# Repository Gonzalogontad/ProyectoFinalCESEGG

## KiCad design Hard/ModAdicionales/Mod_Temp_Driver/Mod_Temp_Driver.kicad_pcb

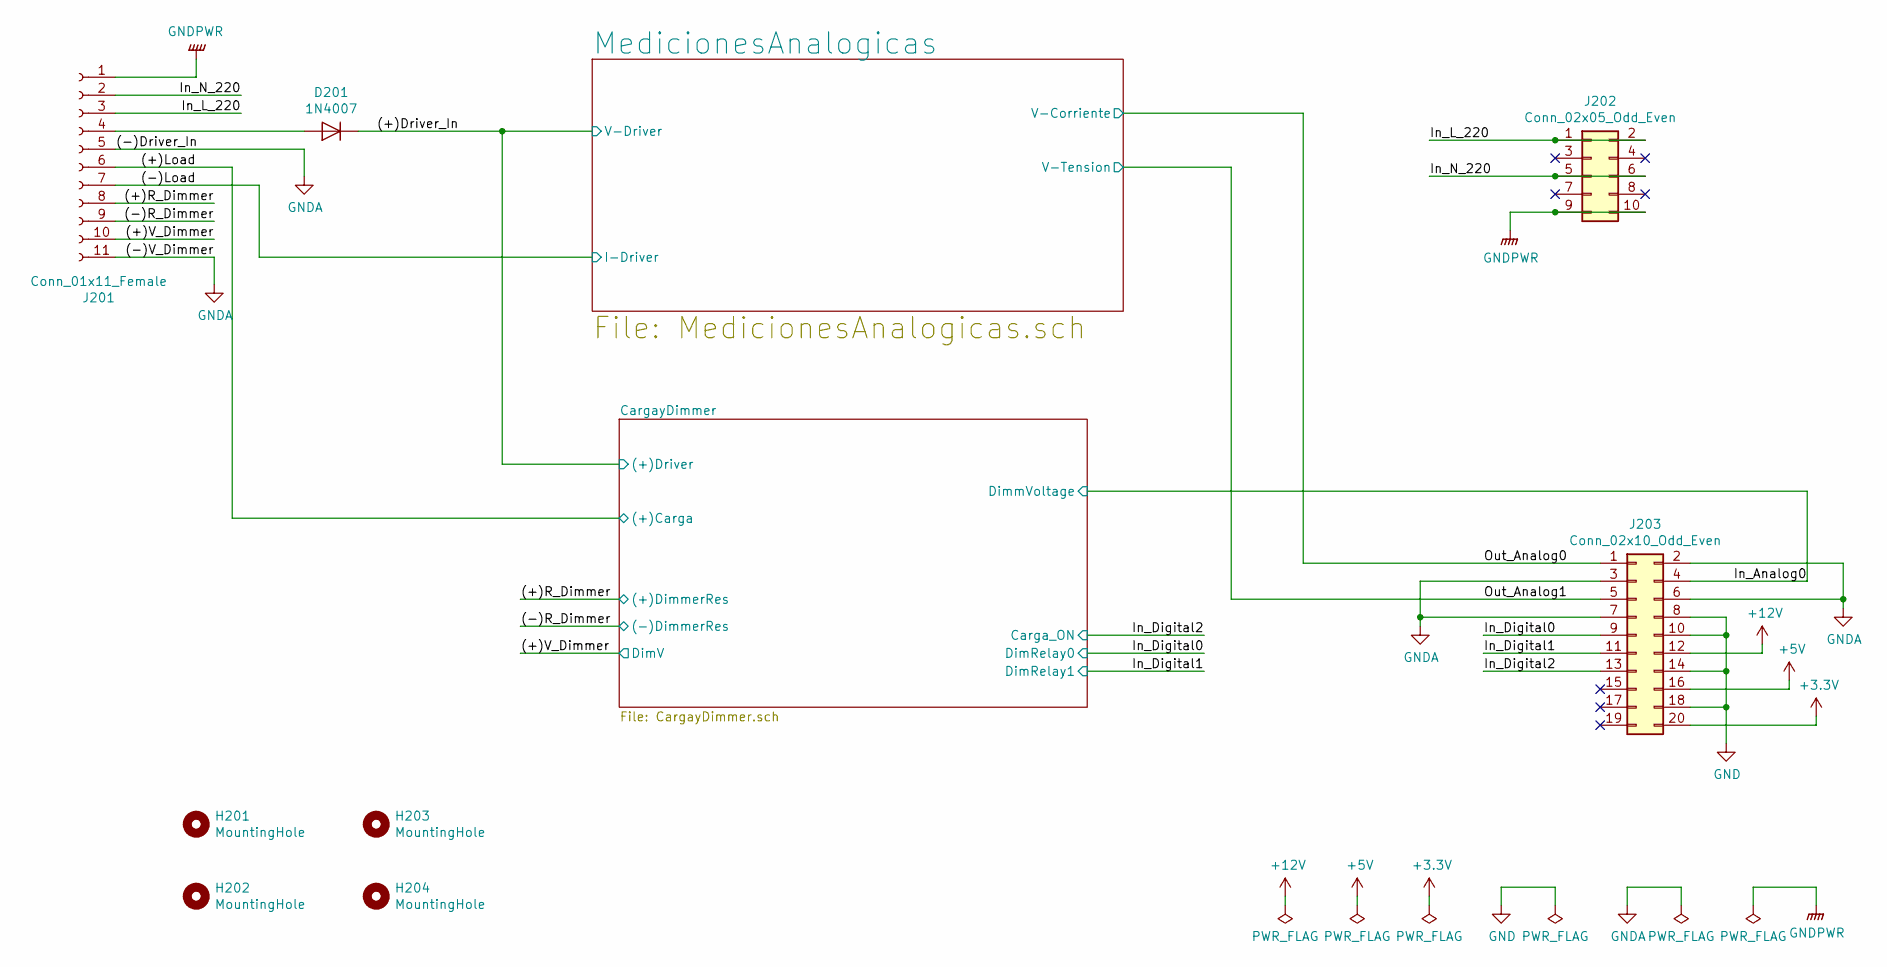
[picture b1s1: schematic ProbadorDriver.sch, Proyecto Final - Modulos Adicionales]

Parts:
D201: 1N4007; D_DO-41_SOD81_P10.16mm_Horizontal
H201, H202, H203, H204: MountingHole; MountingHole_3.2mm_M3
J201: Conn_01x11_Female; TerminalBlock_bornier-11_P5.00mm
J202: Conn_02x05_Odd_Even; PinHeader_2x05_P2.54mm_Horizontal
J203: Conn_02x10_Odd_Even; PinHeader_2x10_P2.54mm_Horizontal

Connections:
+3V3: J203.20
+5V: J203.16
+12V: J203.12; also elsewhere on the board
/ProbadorDriver/(+)Driver_In: D201.1 (K); also elsewhere on the board
/ProbadorDriver/(+)Load: J201.6; also elsewhere on the board
/ProbadorDriver/(+)R_Dimmer: J201.8; also elsewhere on the board
/ProbadorDriver/(+)V_Dimmer: J201.10; also elsewhere on the board
/ProbadorDriver/(-)Load: J201.7; also elsewhere on the board
/ProbadorDriver/(-)R_Dimmer: J201.9; also elsewhere on the board
/ProbadorDriver/In_Analog0: J203.4; also elsewhere on the board
/ProbadorDriver/In_Digital0: J203.9; also elsewhere on the board
/ProbadorDriver/In_Digital1: J203.11; also elsewhere on the board
/ProbadorDriver/In_Digital2: J203.13; also elsewhere on the board
/ProbadorDriver/In_L_220: J201.3, J202.1, J202.2
/ProbadorDriver/In_N_220: J201.2, J202.5, J202.6
/ProbadorDriver/Out_Analog0: J203.1; also elsewhere on the board
/ProbadorDriver/Out_Analog1: J203.5; also elsewhere on the board
GND: J203.8, J203.10, J203.14, J203.18; also elsewhere on the board
GNDA: J201.5, J201.11, J203.2, J203.3, J203.6, J203.7; also elsewhere on the board
GNDPWR: J201.1, J202.9, J202.10
unnamed: D201.2 (A), J201.4

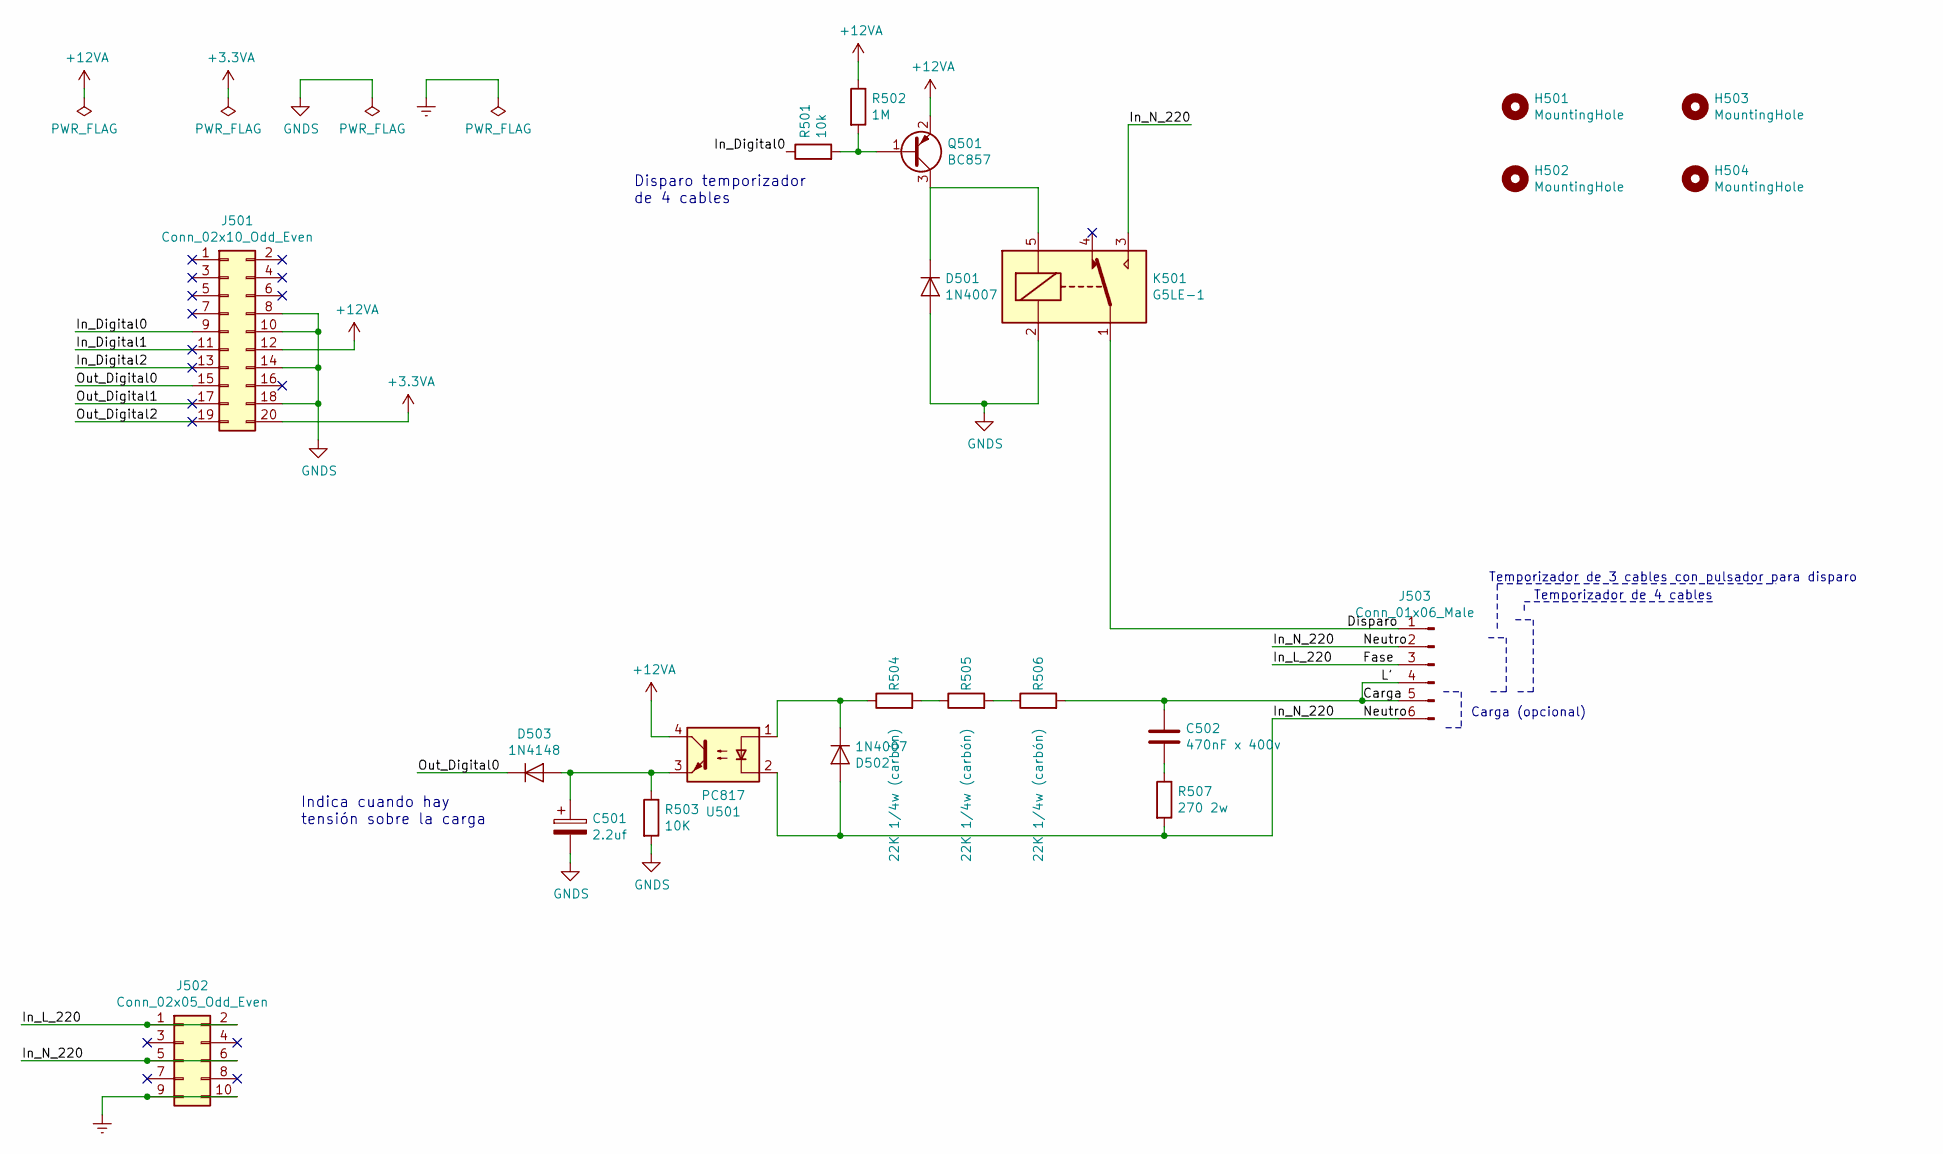
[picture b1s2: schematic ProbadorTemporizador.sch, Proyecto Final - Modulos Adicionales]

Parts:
C501: 2.2uf; CP_Radial_D5.0mm_P2.00mm
C502: 470nF x 400v; C_Rect_L16.5mm_W8.7mm_P15.00mm_MKT
D501, D502: 1N4007; D_DO-41_SOD81_P10.16mm_Horizontal
D503: 1N4148; D_MiniMELF
H501, H502, H503, H504: MountingHole; MountingHole_3.2mm_M3
J501: Conn_02x10_Odd_Even; PinHeader_2x10_P2.54mm_Horizontal
J502: Conn_02x05_Odd_Even; PinHeader_2x05_P2.54mm_Horizontal
J503: Conn_01x06_Male; TerminalBlock_bornier-6_P5.00mm
K501: G5LE-1; Relay_SPDT_Omron-G5LE-1
Q501: BC857; SOT-23
R501: 10k; R_0805_2012Metric_Pad1.15x1.40mm_HandSolder
R502: 1M; R_0805_2012Metric_Pad1.15x1.40mm_HandSolder
R503: 10K; R_0805_2012Metric_Pad1.15x1.40mm_HandSolder
R504, R505, R506: 22K 1/4w (carbón); R_Axial_DIN0207_L6.3mm_D2.5mm_P7.62mm_Horizontal
R507: 270 2w; R_Axial_DIN0516_L15.5mm_D5.0mm_P20.32mm_Horizontal
U501: PC817; DIP-4_W7.62mm

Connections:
+3.3VA: J501.20
+12VA: J501.12, Q501.2 (E), R502.1, U501.4
/ProbadorTemporizador/Carga: C502.1, J503.4, J503.5, R506.2
/ProbadorTemporizador/Disparo: J503.1, K501.1
/ProbadorTemporizador/Fase: J502.1, J502.2, J503.3
/ProbadorTemporizador/In_Digital0: J501.9, R501.1
/ProbadorTemporizador/In_Digital1: J501.11
/ProbadorTemporizador/In_Digital2: J501.13
/ProbadorTemporizador/In_N_220: D502.2 (A), J502.5, J502.6, J503.2, J503.6, K501.3, R507.2, U501.2
/ProbadorTemporizador/Out_Digital0: D503.1 (K), J501.15
/ProbadorTemporizador/Out_Digital1: J501.17
/ProbadorTemporizador/Out_Digital2: J501.19
Earth: J502.9, J502.10
GNDS: C501.2, D501.2 (A), J501.8, J501.10, J501.14, J501.18, K501.2, R503.2
unnamed: C501.1, D503.2 (A), R503.1, U501.3
unnamed: C502.2, R507.1
unnamed: D501.1 (K), K501.5, Q501.3 (C)
unnamed: D502.1 (K), R504.1, U501.1
unnamed: Q501.1 (B), R501.2, R502.2
unnamed: R504.2, R505.1
unnamed: R505.2, R506.1

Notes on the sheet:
Carga (opcional)
Temporizador de 3 cables con pulsador para disparo
Temporizador de 4 cables
Disparo temporizador de 4 cables
Indica cuando hay tensión sobre la carga

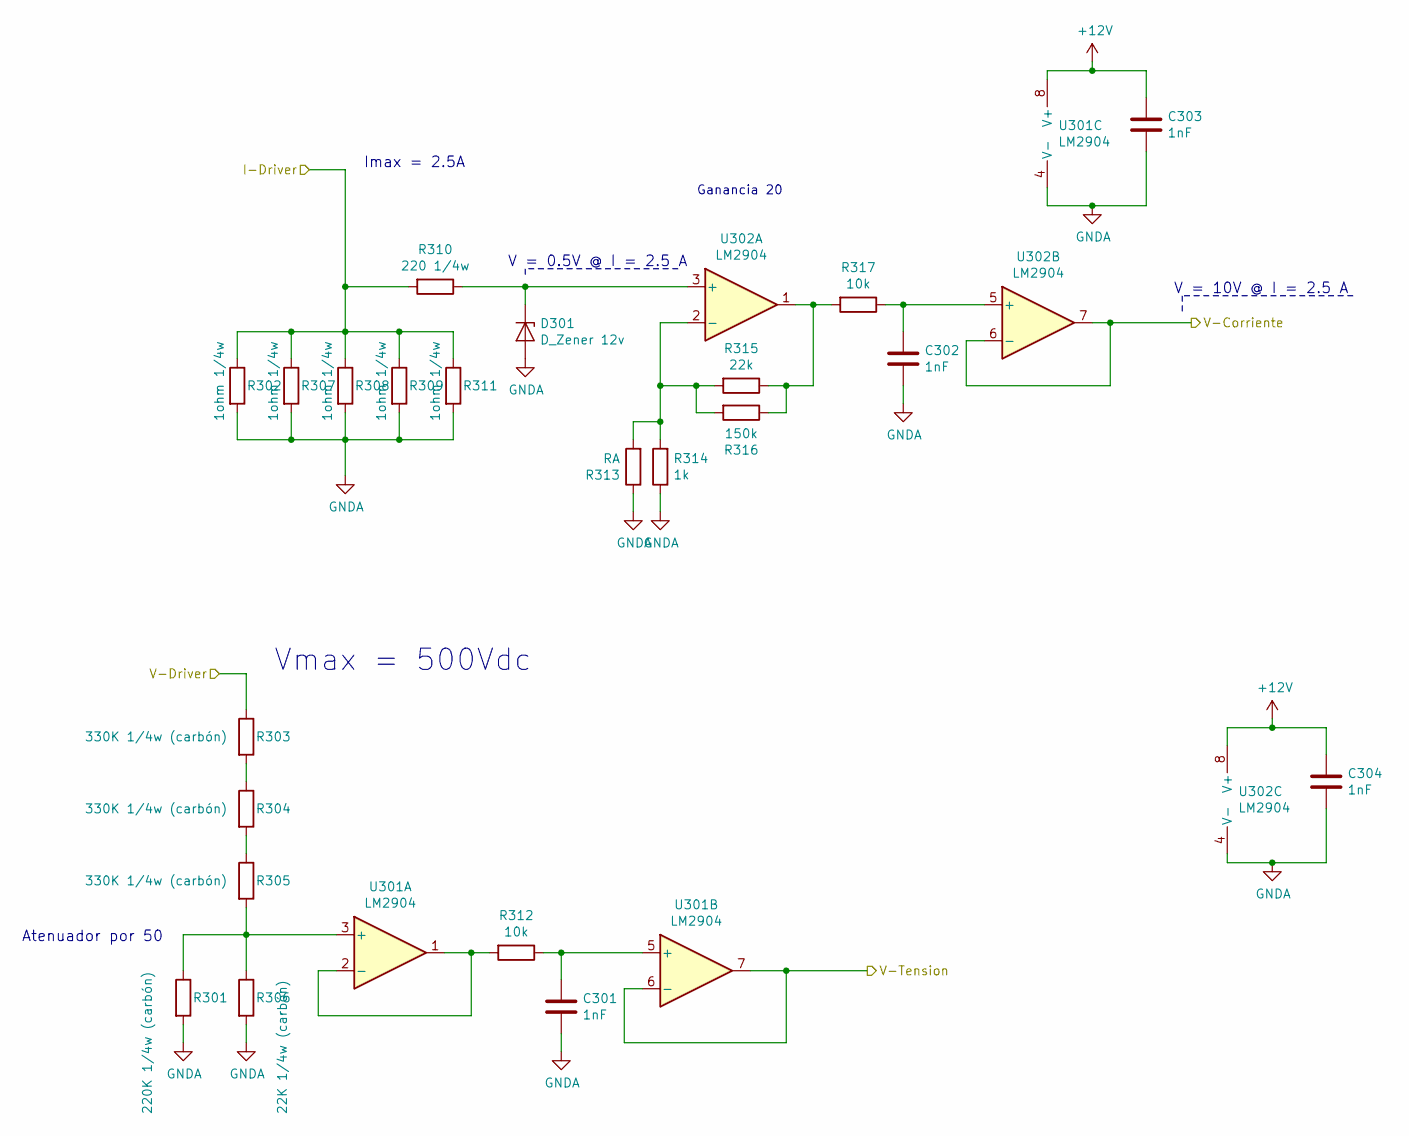
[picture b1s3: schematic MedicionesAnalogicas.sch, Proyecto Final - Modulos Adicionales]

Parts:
C301, C302, C303, C304: 1nF; C_0805_2012Metric_Pad1.15x1.40mm_HandSolder
D301: D_Zener 12v; D_DO-35_SOD27_P7.62mm_Horizontal
R301: 220K 1/4w (carbón); R_Axial_DIN0309_L9.0mm_D3.2mm_P12.70mm_Horizontal
R302, R307, R308, R309, R311: 1ohm 1/4w; R_Axial_DIN0309_L9.0mm_D3.2mm_P12.70mm_Horizontal
R303, R304, R305: 330K 1/4w (carbón); R_Axial_DIN0309_L9.0mm_D3.2mm_P12.70mm_Horizontal
R306: 22K 1/4w (carbón); R_Axial_DIN0309_L9.0mm_D3.2mm_P12.70mm_Horizontal
R310: 220 1/4w; R_Axial_DIN0309_L9.0mm_D3.2mm_P12.70mm_Horizontal
R312, R317: 10k; R_0805_2012Metric_Pad1.15x1.40mm_HandSolder
R313: RA; R_0805_2012Metric_Pad1.15x1.40mm_HandSolder
R314: 1k; R_0805_2012Metric_Pad1.15x1.40mm_HandSolder
R315: 22k; R_0805_2012Metric_Pad1.15x1.40mm_HandSolder
R316: 150k; R_0805_2012Metric_Pad1.15x1.40mm_HandSolder
U301, U302: LM2904; SO-8_3.9x4.9mm_P1.27mm

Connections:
+12V: C303.1, C304.1, U301.8 (V+), U302.8 (V+); also elsewhere on the board
/ProbadorDriver/(+)Driver_In: R303.1; also elsewhere on the board
/ProbadorDriver/(-)Load: R302.1, R307.1, R308.1, R309.1, R310.2, R311.1; also elsewhere on the board
/ProbadorDriver/Out_Analog0: U302.6 (-), U302.7; also elsewhere on the board
/ProbadorDriver/Out_Analog1: U301.6 (-), U301.7; also elsewhere on the board
GNDA: C301.2, C302.2, C303.2, C304.2, D301.2 (A), R301.2, R302.2, R306.2, R307.2, R308.2, R309.2, R311.2, R313.1, R314.1, U301.4 (V-), U302.4 (V-); also elsewhere on the board
unnamed: C301.1, R312.1, U301.5 (+)
unnamed: C302.1, R317.1, U302.5 (+)
unnamed: D301.1 (K), R310.1, U302.3 (+)
unnamed: R301.1, R305.2, R306.1, U301.3 (+)
unnamed: R303.2, R304.1
unnamed: R304.2, R305.1
unnamed: R312.2, U301.1, U301.2 (-)
unnamed: R313.2, R314.2, R315.2, R316.2, U302.2 (-)
unnamed: R315.1, R316.1, R317.2, U302.1

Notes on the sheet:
Ganancia 20
Vmax = 500Vdc
Atenuador por 50
Imax = 2.5A
V = 0.5V @ I = 2.5 A
V = 10V @ I = 2.5 A

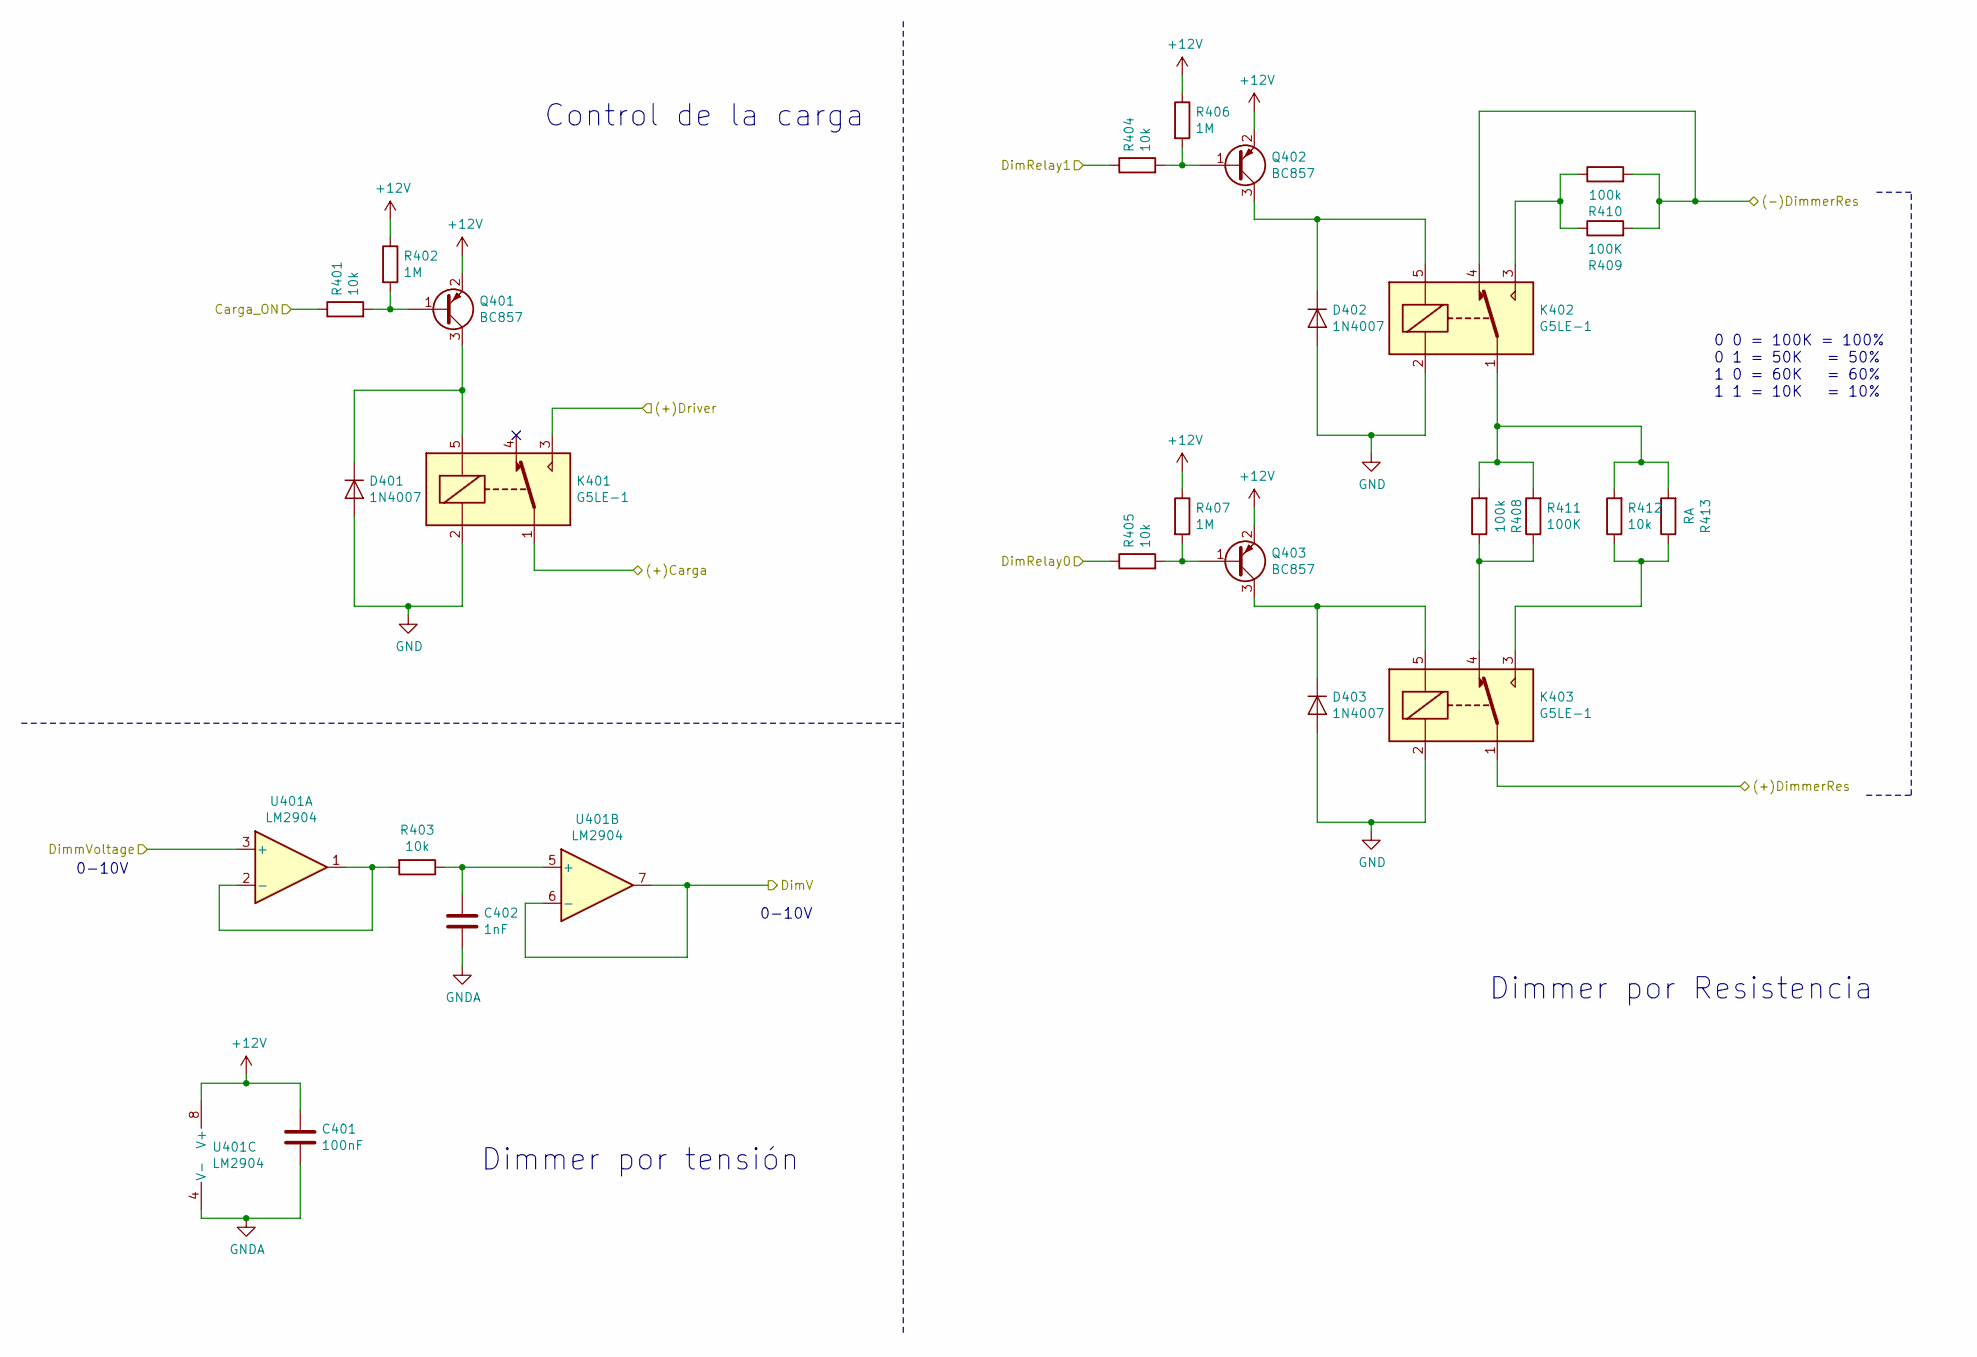
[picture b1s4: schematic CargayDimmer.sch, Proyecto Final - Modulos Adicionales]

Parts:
C401: 100nF; C_0805_2012Metric_Pad1.15x1.40mm_HandSolder
C402: 1nF; C_0805_2012Metric_Pad1.15x1.40mm_HandSolder
D401, D402, D403: 1N4007; D_DO-41_SOD81_P10.16mm_Horizontal
K401, K402, K403: G5LE-1; Relay_SPDT_Omron-G5LE-1
Q401, Q402, Q403: BC857; SOT-23
R401, R403, R404, R405, R412: 10k; R_0805_2012Metric_Pad1.15x1.40mm_HandSolder
R402, R406, R407: 1M; R_0805_2012Metric_Pad1.15x1.40mm_HandSolder
R408, R410: 100k; R_0805_2012Metric_Pad1.15x1.40mm_HandSolder
R409, R411: 100K; R_0805_2012Metric_Pad1.15x1.40mm_HandSolder
R413: RA; R_0805_2012Metric_Pad1.15x1.40mm_HandSolder
U401: LM2904; SO-8_3.9x4.9mm_P1.27mm

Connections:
+12V: C401.1, Q401.2 (E), Q402.2 (E), Q403.2 (E), R402.1, R406.1, R407.1, U401.8 (V+); also elsewhere on the board
/ProbadorDriver/(+)Driver_In: K401.3; also elsewhere on the board
/ProbadorDriver/(+)Load: K401.1; also elsewhere on the board
/ProbadorDriver/(+)R_Dimmer: K403.1; also elsewhere on the board
/ProbadorDriver/(+)V_Dimmer: U401.6 (-), U401.7; also elsewhere on the board
/ProbadorDriver/(-)R_Dimmer: K402.4, R409.2, R410.2; also elsewhere on the board
/ProbadorDriver/In_Analog0: U401.3 (+); also elsewhere on the board
/ProbadorDriver/In_Digital0: R405.1; also elsewhere on the board
/ProbadorDriver/In_Digital1: R404.1; also elsewhere on the board
/ProbadorDriver/In_Digital2: R401.1; also elsewhere on the board
GND: D401.2 (A), D402.2 (A), D403.2 (A), K401.2, K402.2, K403.2; also elsewhere on the board
GNDA: C401.2, C402.2, U401.4 (V-); also elsewhere on the board
unnamed: C402.1, R403.1, U401.5 (+)
unnamed: D401.1 (K), K401.5, Q401.3 (C)
unnamed: D402.1 (K), K402.5, Q402.3 (C)
unnamed: D403.1 (K), K403.5, Q403.3 (C)
unnamed: K402.1, R408.2, R411.2, R412.2, R413.2
unnamed: K402.3, R409.1, R410.1
unnamed: K403.3, R412.1, R413.1
unnamed: K403.4, R408.1, R411.1
unnamed: Q401.1 (B), R401.2, R402.2
unnamed: Q402.1 (B), R404.2, R406.2
unnamed: Q403.1 (B), R405.2, R407.2
unnamed: R403.2, U401.1, U401.2 (-)

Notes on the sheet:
Control de la carga
Dimmer por tensión
Dimmer por Resistencia
0-10V
0 0 = 100K = 100% 0 1 = 50K = 50% 1 0 = 60K = 60% 1 1 = 10K = 10%

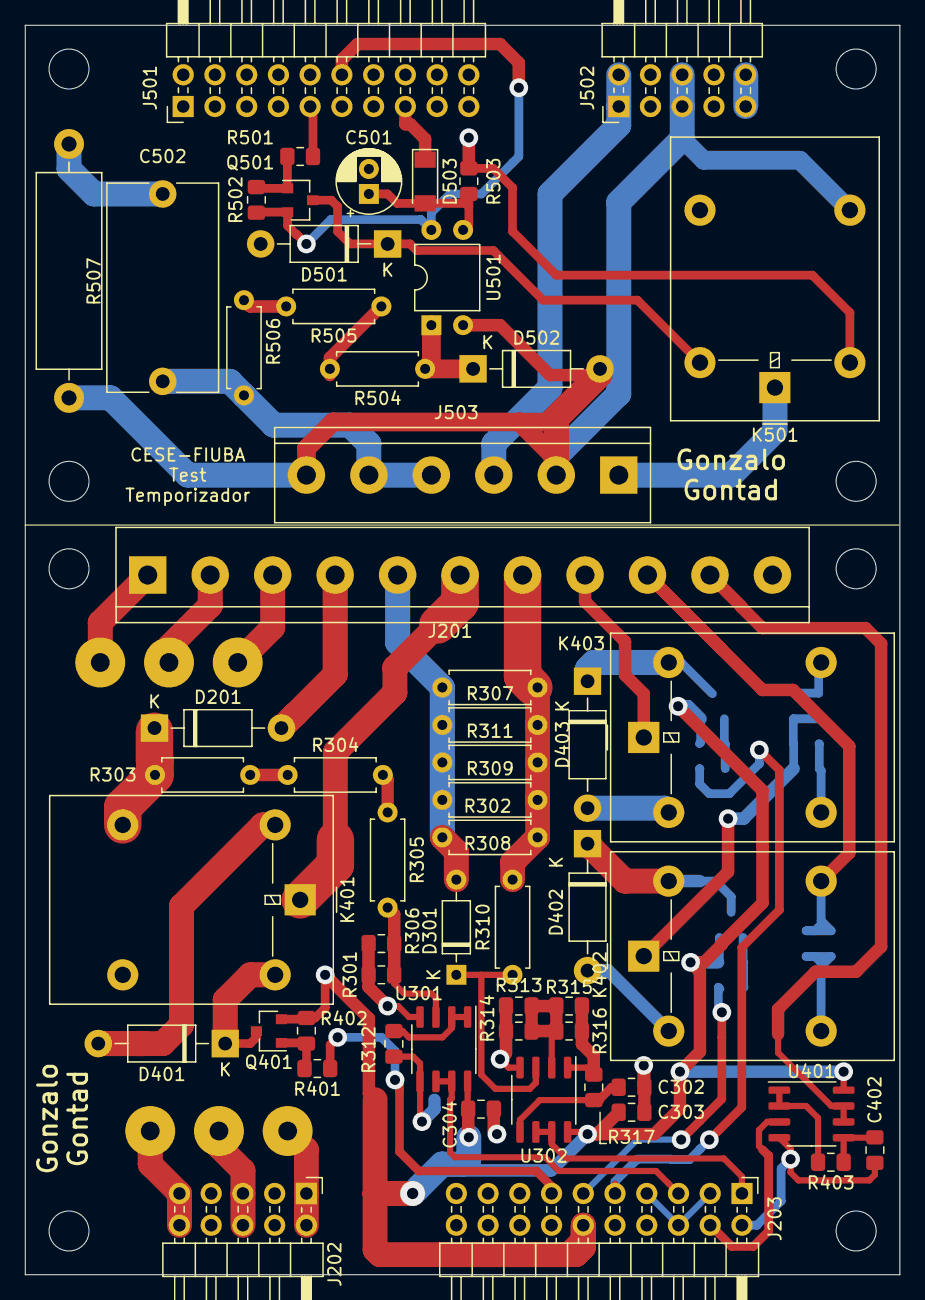
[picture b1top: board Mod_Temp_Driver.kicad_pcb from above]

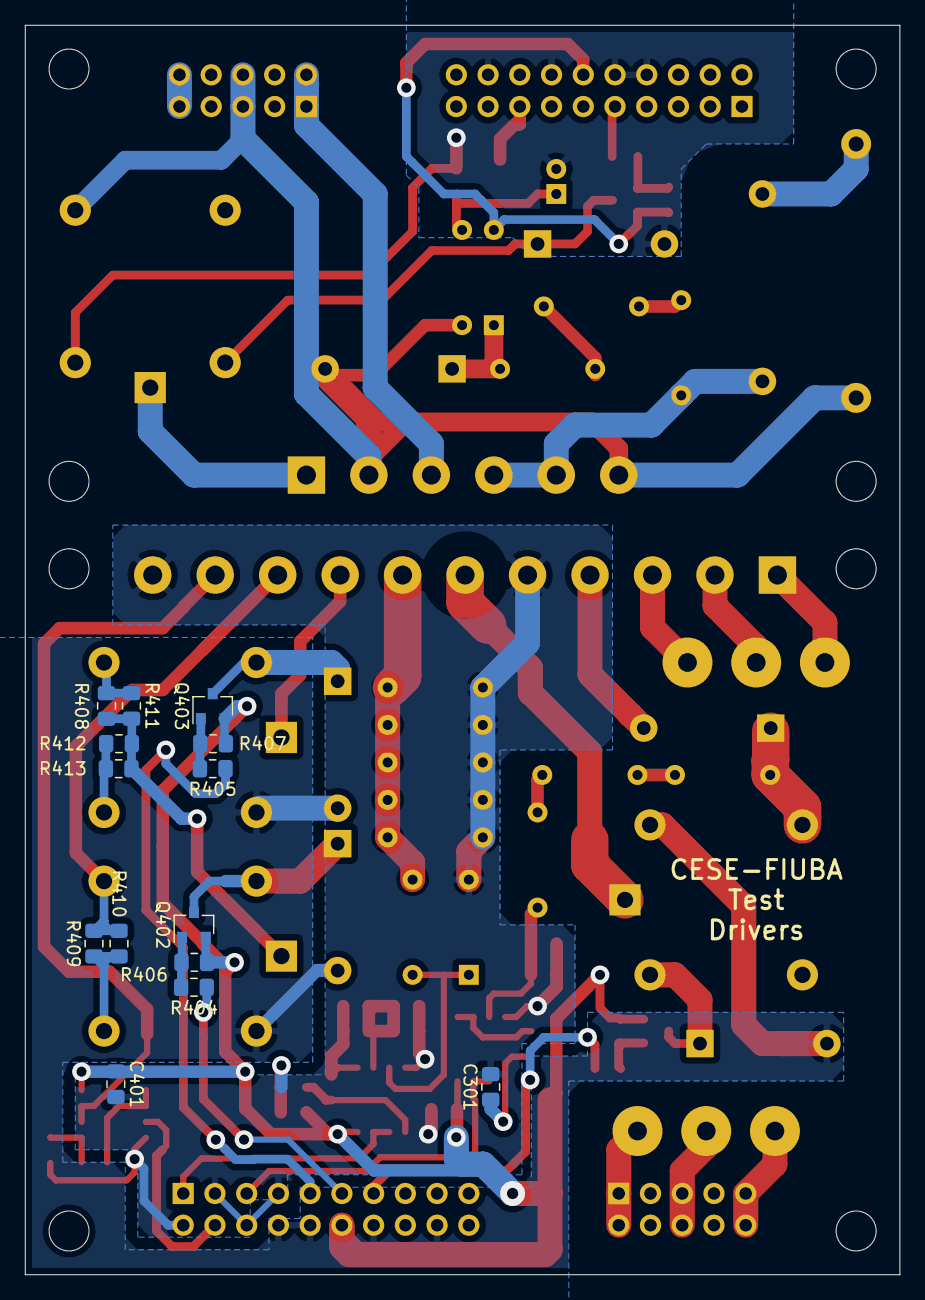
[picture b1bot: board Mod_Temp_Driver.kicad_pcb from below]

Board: 2 copper layers, 70.0 x 100.0 mm, 79 parts (14 on the bottom side), 56 nets.

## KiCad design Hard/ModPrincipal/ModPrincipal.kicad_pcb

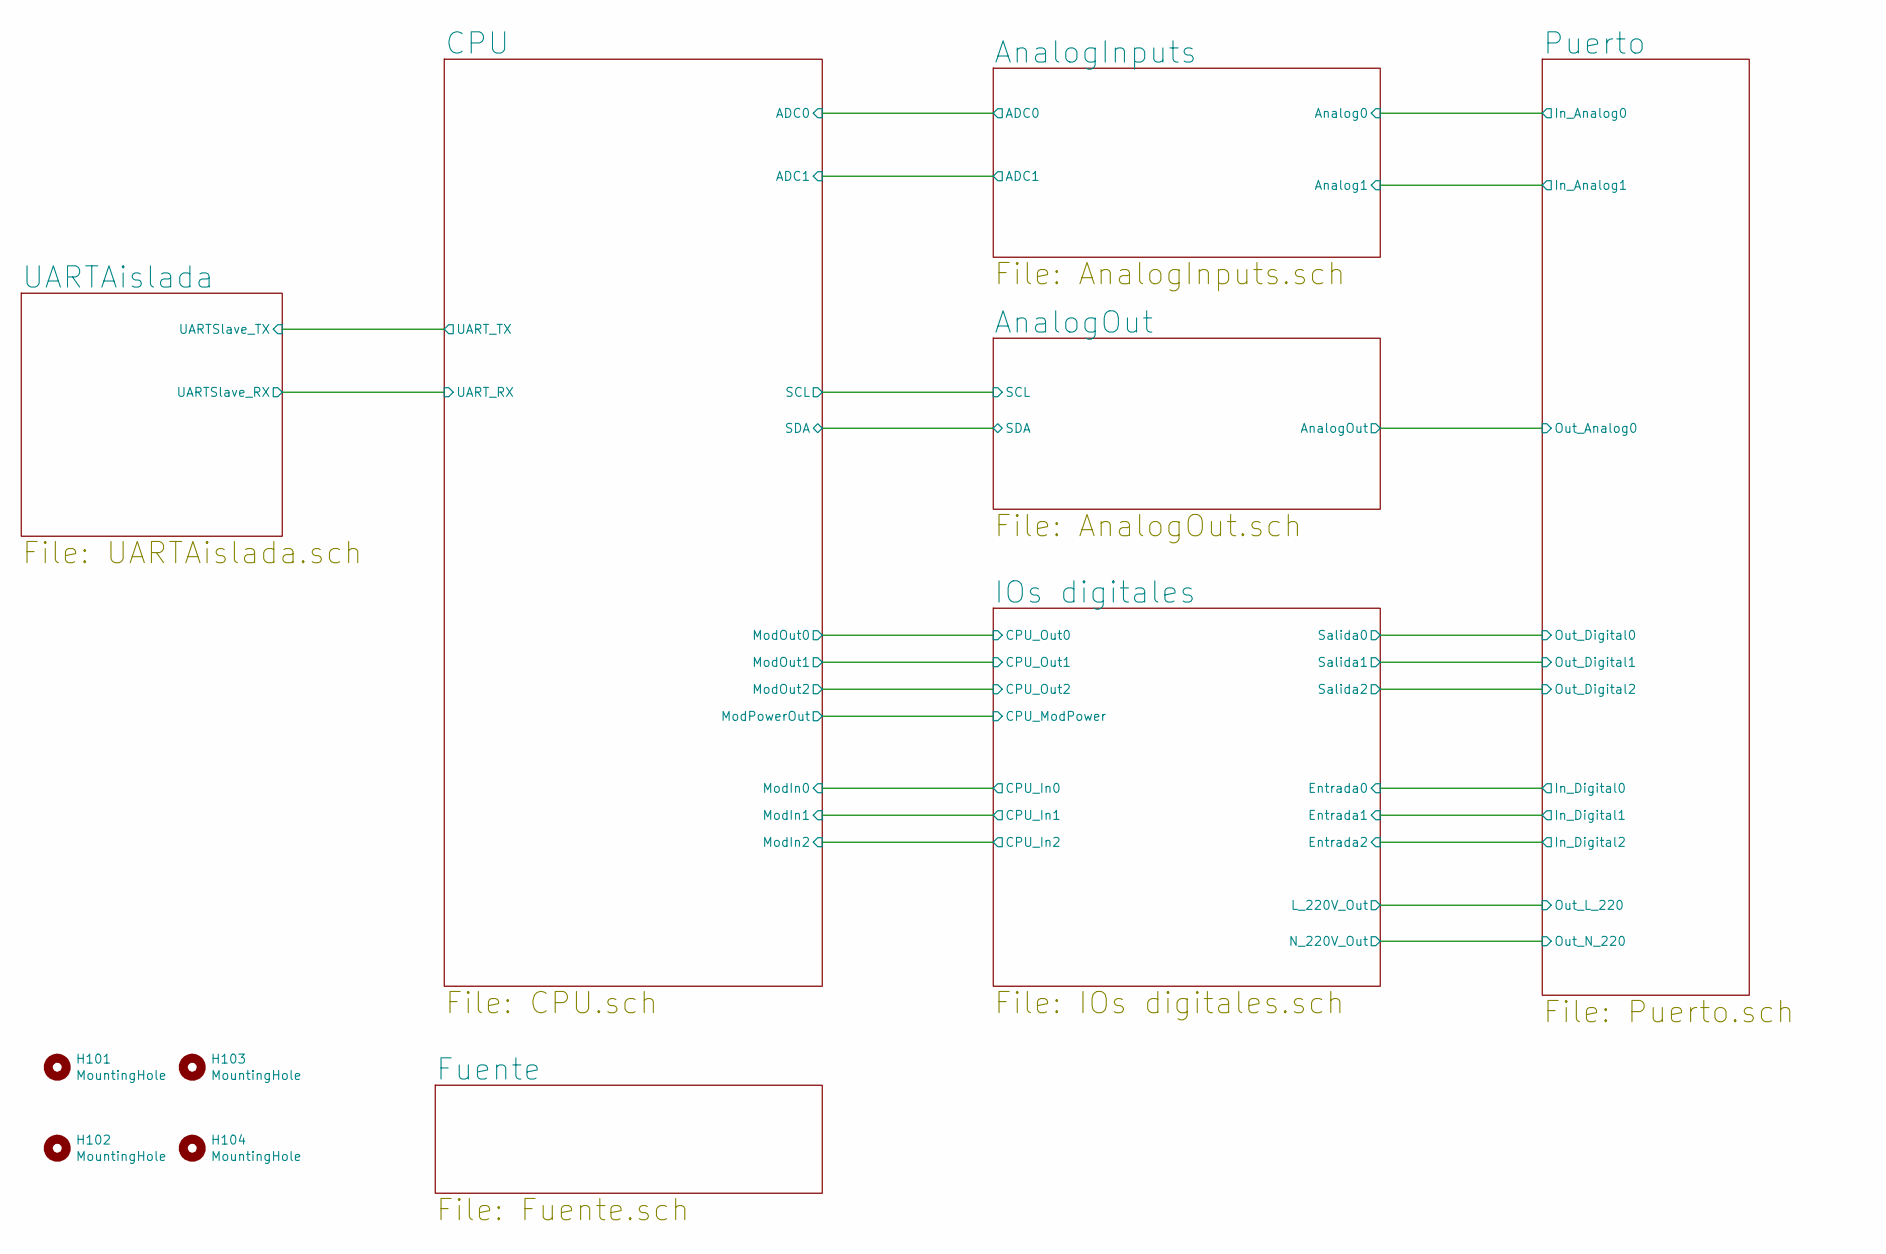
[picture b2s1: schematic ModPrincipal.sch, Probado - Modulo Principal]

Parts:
H101, H102, H103, H104: MountingHole; MountingHole_3.2mm_M3

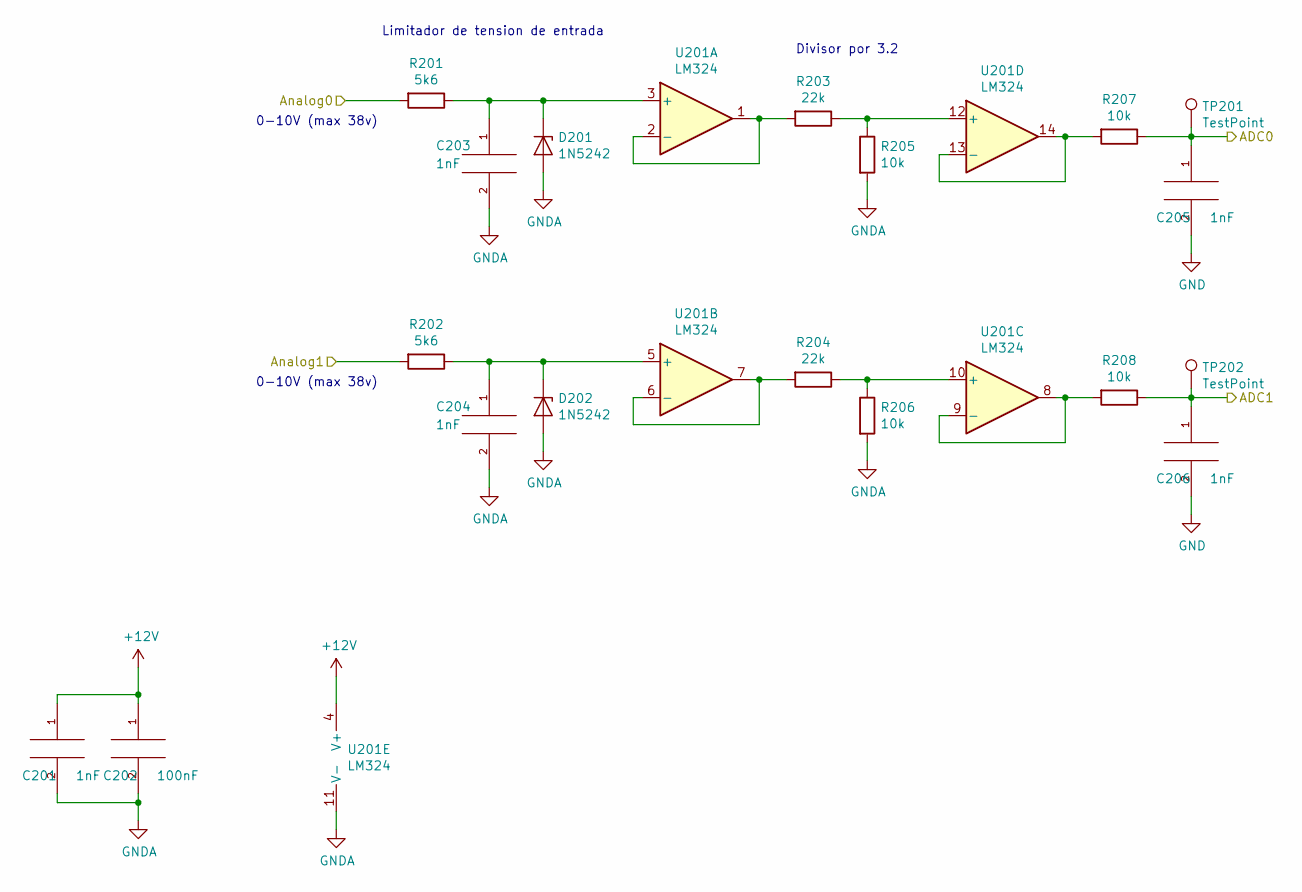
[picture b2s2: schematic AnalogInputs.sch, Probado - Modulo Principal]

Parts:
C201, C203, C204, C205, C206: 1nF; C_0805_2012Metric_Pad1.15x1.40mm_HandSolder
C202: 100nF; C_0805_2012Metric_Pad1.15x1.40mm_HandSolder
D201, D202: 1N5242; D_DO-35_SOD27_P7.62mm_Horizontal
R201, R202: 5k6; R_0805_2012Metric_Pad1.15x1.40mm_HandSolder
R203, R204: 22k; R_0805_2012Metric_Pad1.15x1.40mm_HandSolder
R205, R206, R207, R208: 10k; R_0805_2012Metric_Pad1.15x1.40mm_HandSolder
TP201, TP202: TestPoint; TestPoint_Pad_D1.5mm
U201: LM324; SOIC-14_3.9x8.7mm_P1.27mm

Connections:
+12V: C201.1, C202.1, U201.4 (V+); also elsewhere on the board
/AnalogInputs/ADC0: C205.1, R207.1, TP201.1; also elsewhere on the board
/AnalogInputs/ADC1: C206.1, R208.1, TP202.1; also elsewhere on the board
/AnalogInputs/Analog0: R201.2; also elsewhere on the board
/AnalogInputs/Analog1: R202.2; also elsewhere on the board
GND: C205.2, C206.2; also elsewhere on the board
GNDA: C201.2, C202.2, C203.2, C204.2, D201.2 (A), D202.2 (A), R205.2, R206.2, U201.11 (V-); also elsewhere on the board
unnamed: C203.1, D201.1 (K), R201.1, U201.3 (+)
unnamed: C204.1, D202.1 (K), R202.1, U201.5 (+)
unnamed: R203.1, R205.1, U201.12 (+)
unnamed: R203.2, U201.1, U201.2 (-)
unnamed: R204.1, R206.1, U201.10 (+)
unnamed: R204.2, U201.6 (-), U201.7
unnamed: R207.2, U201.13 (-), U201.14
unnamed: R208.2, U201.8, U201.9 (-)

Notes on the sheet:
0-10V (max 38v)
Divisor por 3.2
Limitador de tension de entrada

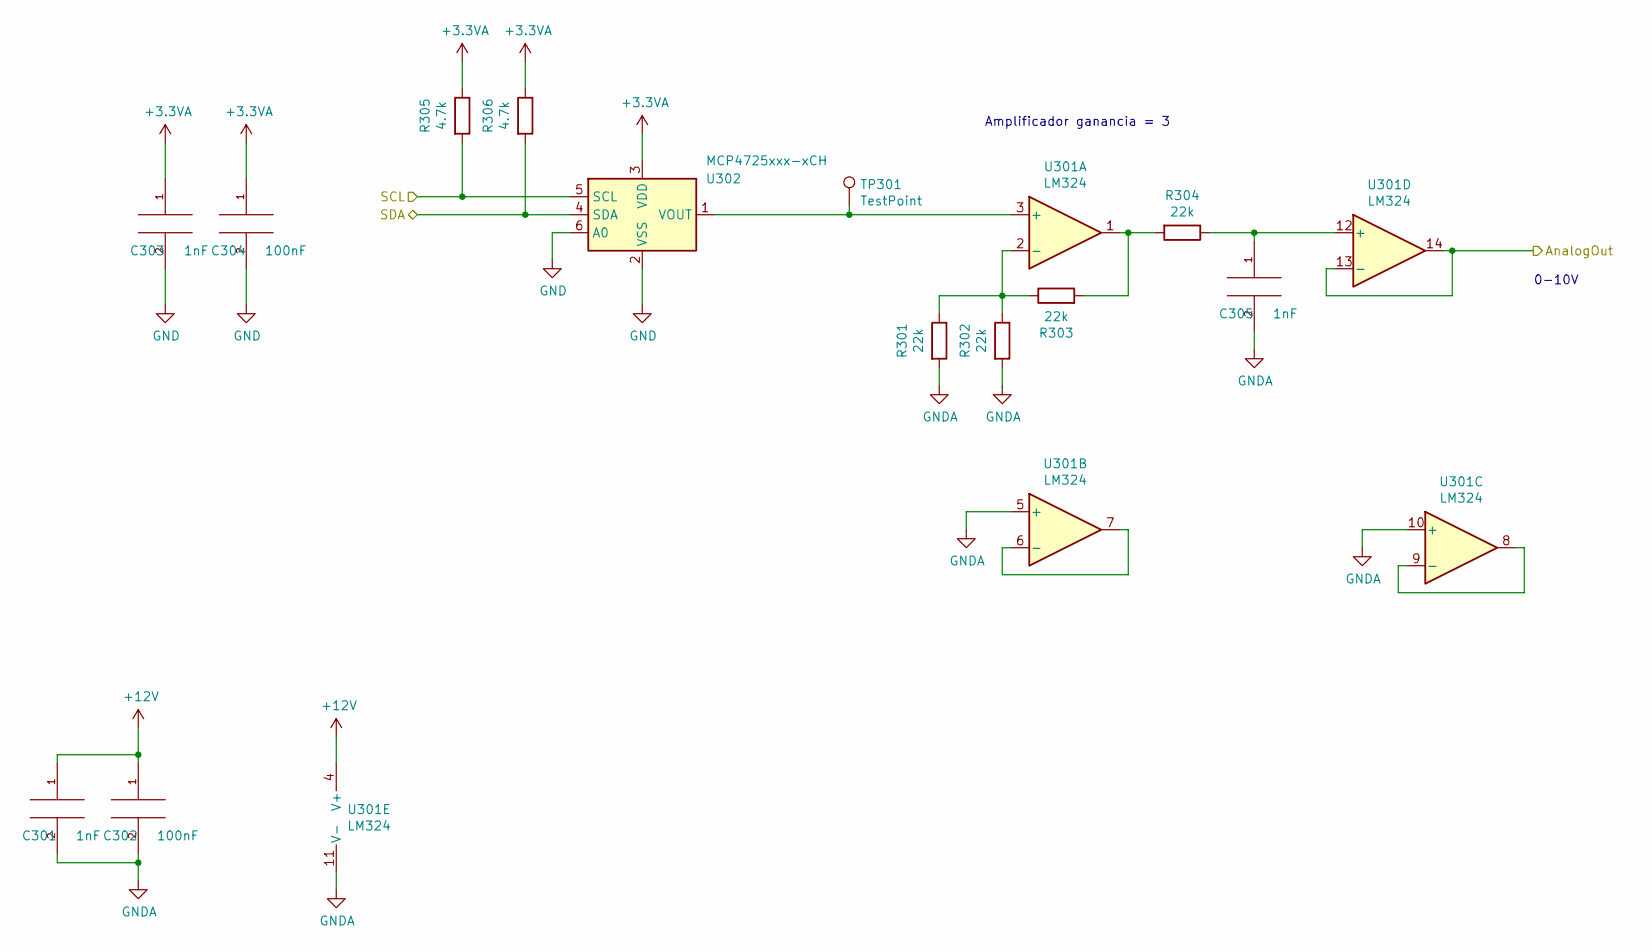
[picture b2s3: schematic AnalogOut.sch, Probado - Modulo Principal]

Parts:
C301, C303, C305: 1nF; C_0805_2012Metric_Pad1.15x1.40mm_HandSolder
C302, C304: 100nF; C_0805_2012Metric_Pad1.15x1.40mm_HandSolder
R301, R302, R303, R304: 22k; R_0805_2012Metric_Pad1.15x1.40mm_HandSolder
R305, R306: 4.7k; R_0805_2012Metric_Pad1.15x1.40mm_HandSolder
TP301: TestPoint; TestPoint_Pad_D1.5mm
U301: LM324; SOIC-14_3.9x8.7mm_P1.27mm
U302: MCP4725xxx-xCH; SOT-23-6

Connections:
+3.3VA: C303.1, C304.1, R305.1, R306.1, U302.3 (VDD); also elsewhere on the board
+12V: C301.1, C302.1, U301.4 (V+); also elsewhere on the board
/AnalogOut/AnalogOut: U301.13 (-), U301.14; also elsewhere on the board
/AnalogOut/SCL: R305.2, U302.5 (SCL); also elsewhere on the board
/AnalogOut/SDA: R306.2, U302.4 (SDA); also elsewhere on the board
GND: C303.2, C304.2, U302.2 (VSS), U302.6 (A0); also elsewhere on the board
GNDA: C301.2, C302.2, C305.2, R301.2, R302.2, U301.5 (+), U301.10 (+), U301.11 (V-); also elsewhere on the board
unnamed: C305.1, R304.1, U301.12 (+)
unnamed: R301.1, R302.1, R303.1, U301.2 (-)
unnamed: R303.2, R304.2, U301.1
unnamed: TP301.1, U301.3 (+), U302.1 (VOUT)
unnamed: U301.6 (-), U301.7
unnamed: U301.8, U301.9 (-)

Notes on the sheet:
Amplificador ganancia = 3
0-10V
